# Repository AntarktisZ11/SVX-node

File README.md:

# SA6MBO SVX-node
A basic UHF or VHF node designed around a SA868 fitted as a HAT on top of an [Orange Pi Zero LTS](http://www.orangepi.org/html/hardWare/computerAndMicrocontrollers/details/Orange-Pi-Zero-LTS.html "Orange Pi Zero LTS"). The repeater software is the [SVXLink project](https://github.com/sm0svx/svxlink "SVXLink project") with configuration inspired by the [ROLink community](http://www.439100.ro/ "ROLink community"). The origin of this project is courtesy of [SM6TZL](https://svxportal.sm2ampr.net/station_info.php?callsign=SM6TZL&no_header=true "SM6TZL")'s small mobile unit. A massive praise goes to VoltLogs [VoltNode](https://github.com/voltlog/VoltNode "VoltNode") for comprising the work into a manageable PCB along with short but good documentation.

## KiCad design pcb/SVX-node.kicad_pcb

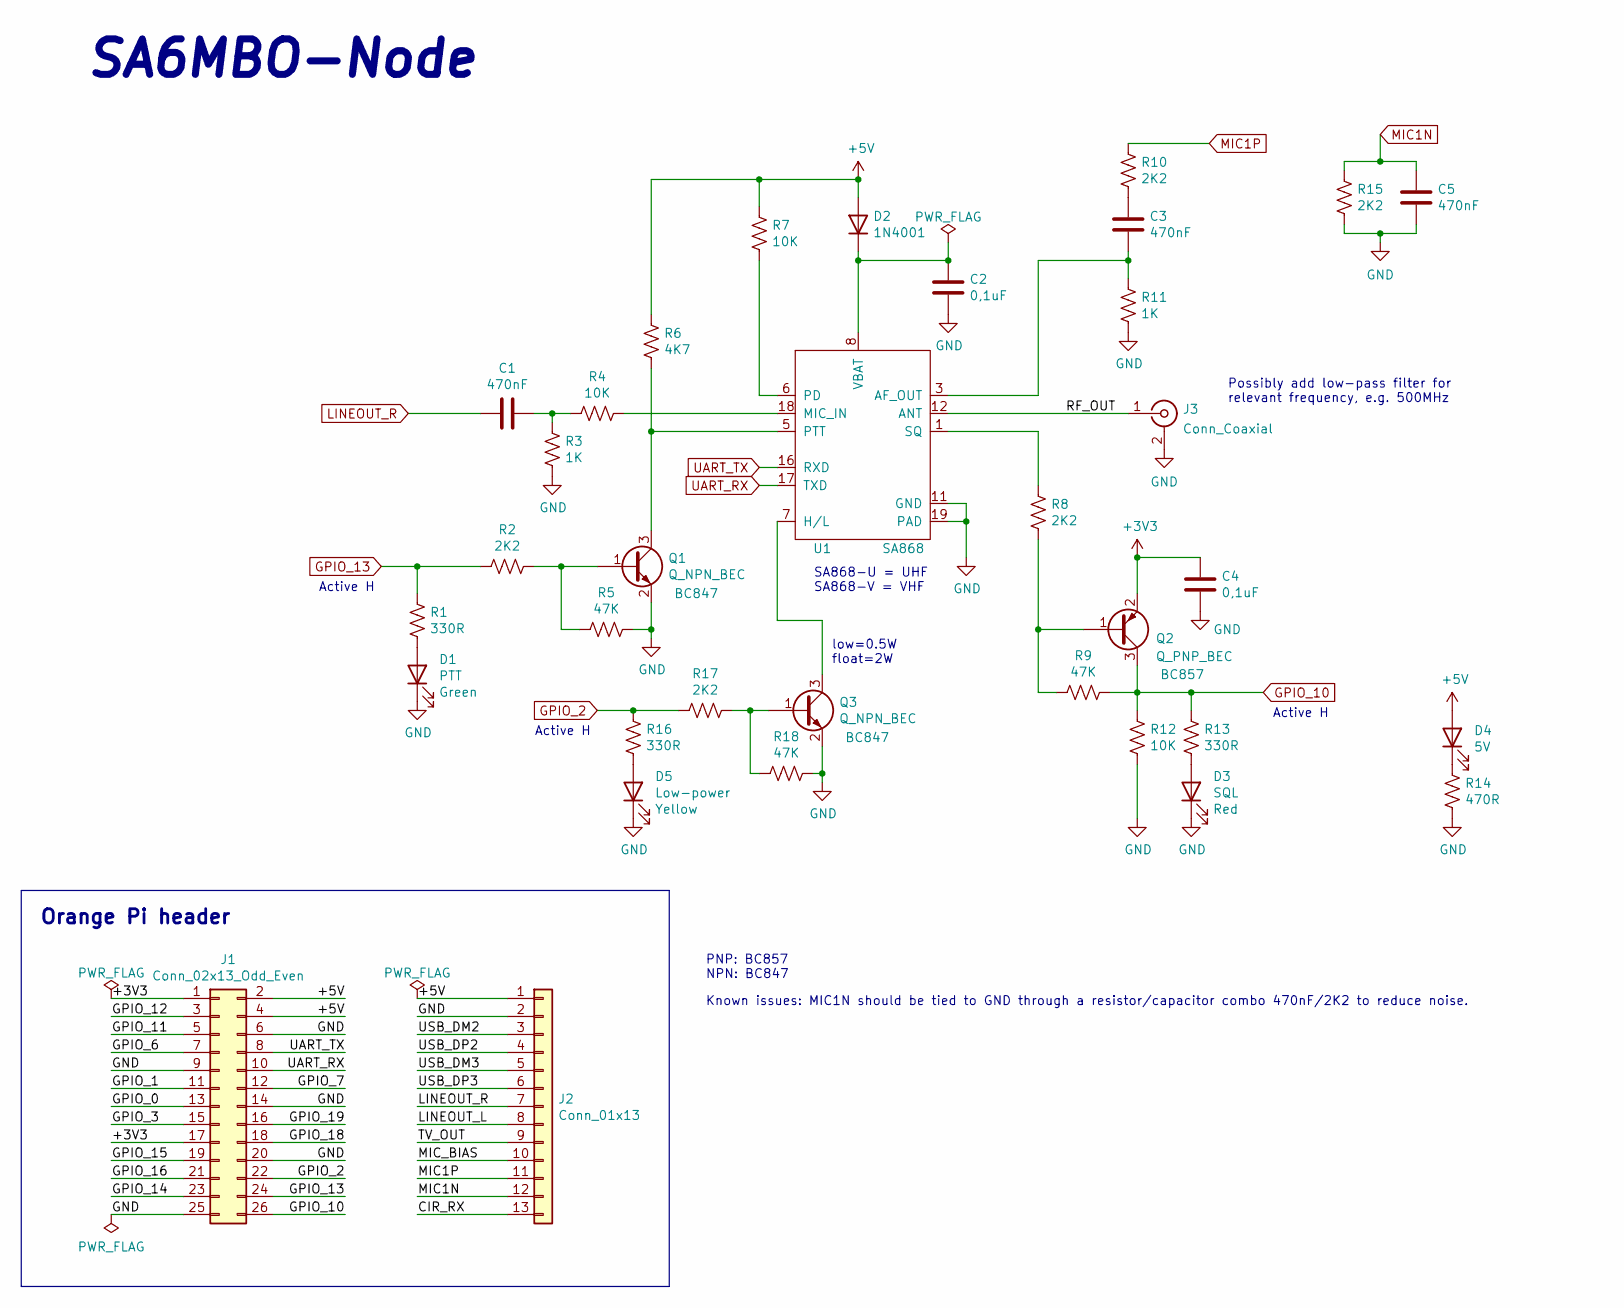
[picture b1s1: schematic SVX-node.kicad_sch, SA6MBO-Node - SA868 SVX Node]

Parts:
C1, C3, C5: 470nF; C_0603_1608Metric
C2, C4: 0,1uF; C_0603_1608Metric
D1: PTT; LED_0603_1608Metric
D2: 1N4001; D_DO-41_SOD81_P5.08mm_Vertical_KathodeUp
D3: SQL; LED_0603_1608Metric
D4: 5V; LED_0603_1608Metric
D5: Low-power; LED_0603_1608Metric
J1: Conn_02x13_Odd_Even; PinSocket_2x13_P2.54mm_Vertical
J2: Conn_01x13; PinSocket_1x13_P2.54mm_Vertical
J3: Conn_Coaxial; SMA_Amphenol_132291-12_Vertical
Q1, Q3: Q_NPN_BEC; TO-92_Inline_Wide
Q2: Q_PNP_BEC; TO-92_Inline_Wide
R1, R13, R16: 330R; R_0603_1608Metric
R2, R8, R10, R15, R17: 2K2; R_0603_1608Metric
R3, R11: 1K; R_0603_1608Metric
R4, R7, R12: 10K; R_0603_1608Metric
R5, R18: 47K; R_0603_1608Metric
R6: 4K7; R_0603_1608Metric
R9: 47K; R_Axial_DIN0204_L3.6mm_D1.6mm_P5.08mm_Horizontal
R14: 470R; R_0603_1608Metric
U1: SA868

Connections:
+3V3: C4.1, J1.1, J1.17, Q2.2 (E)
+5V: D2.2 (A), D4.2 (A), J1.2, J1.4, J2.1, R6.1, R7.1
/CIR_RX: J2.13
/GPIO_0: J1.13
/GPIO_1: J1.11
/GPIO_3: J1.15
/GPIO_6: J1.7
/GPIO_7: J1.12
/GPIO_11: J1.5
/GPIO_12: J1.3
/GPIO_14: J1.23
/GPIO_15: J1.19
/GPIO_16: J1.21
/GPIO_18: J1.18
/GPIO_19: J1.16
/LINEOUT_L: J2.8
/MIC_BIAS: J2.10
/RF_OUT: J3.1 (In), U1.12 (ANT)
/TV_OUT: J2.9
/USB_DM2: J2.3
/USB_DM3: J2.5
/USB_DP2: J2.4
/USB_DP3: J2.6
GND: C2.2, C4.2, C5.2, D1.1 (K), D3.1 (K), D5.1 (K), J1.6, J1.9, J1.14, J1.20, J1.25, J2.2, J3.2 (Ext), Q1.2 (E), Q3.2 (E), R3.2, R5.1, R11.2, R12.2, R14.2, R15.2, R18.1, U1.9, U1.10, U1.11 (GND), U1.19 (PAD)
GPIO_2: J1.22, R16.1, R17.2
GPIO_10: J1.26, Q2.3 (C), R9.2, R12.1, R13.1
GPIO_13: J1.24, R1.1, R2.2
LINEOUT_R: C1.2, J2.7
MIC1N: C5.1, J2.12, R15.1
MIC1P: J2.11, R10.1
unnamed: C1.1, R3.1, R4.2
unnamed: C2.1, D2.1 (K), U1.8 (VBAT)
unnamed: C3.1, R10.2
unnamed: C3.2, R11.1, U1.3 (AF_OUT)
unnamed: D1.2 (A), R1.2
unnamed: D3.2 (A), R13.2
unnamed: D4.1 (K), R14.1
unnamed: D5.2 (A), R16.2
unnamed: Q1.1 (B), R2.1, R5.2
unnamed: Q1.3 (C), R6.2, U1.5 (PTT)
unnamed: Q2.1 (B), R8.2, R9.1
unnamed: Q3.1 (B), R17.1, R18.2
unnamed: Q3.3 (C), U1.7 (H/L)
unnamed: R4.1, U1.18 (MIC_IN)
unnamed: R7.2, U1.6 (PD)
unnamed: R8.1, U1.1 (SQ)
UART_RX: J1.10, U1.17 (TXD)
UART_TX: J1.8, U1.16 (RXD)

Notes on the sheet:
PNP: BC857 NPN: BC847
Orange Pi header
Active H
Possibly add low-pass filter for relevant frequency, e.g. 500MHz
Known issues: MIC1N should be tied to GND through a resistor/capacitor combo 470nF/2K2 to reduce noise.
SA868-U = UHF SA868-V = VHF
low=0.5W float=2W
SA6MBO-Node

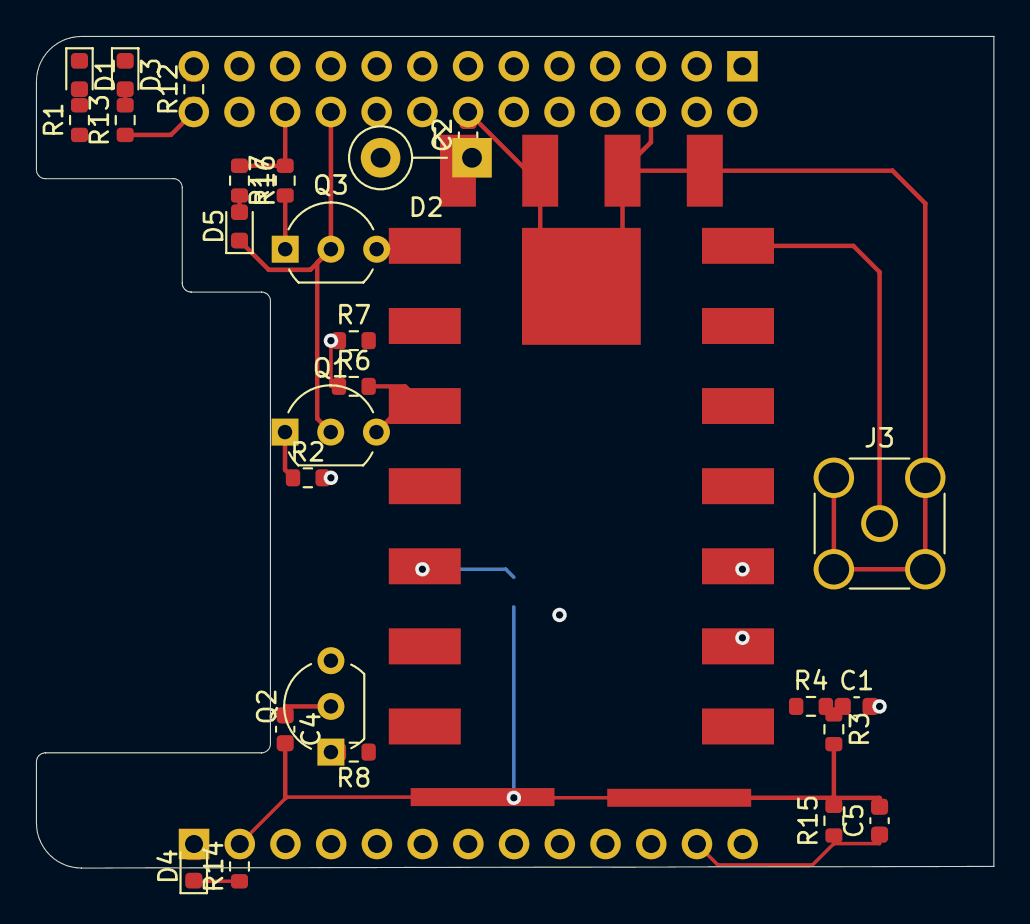
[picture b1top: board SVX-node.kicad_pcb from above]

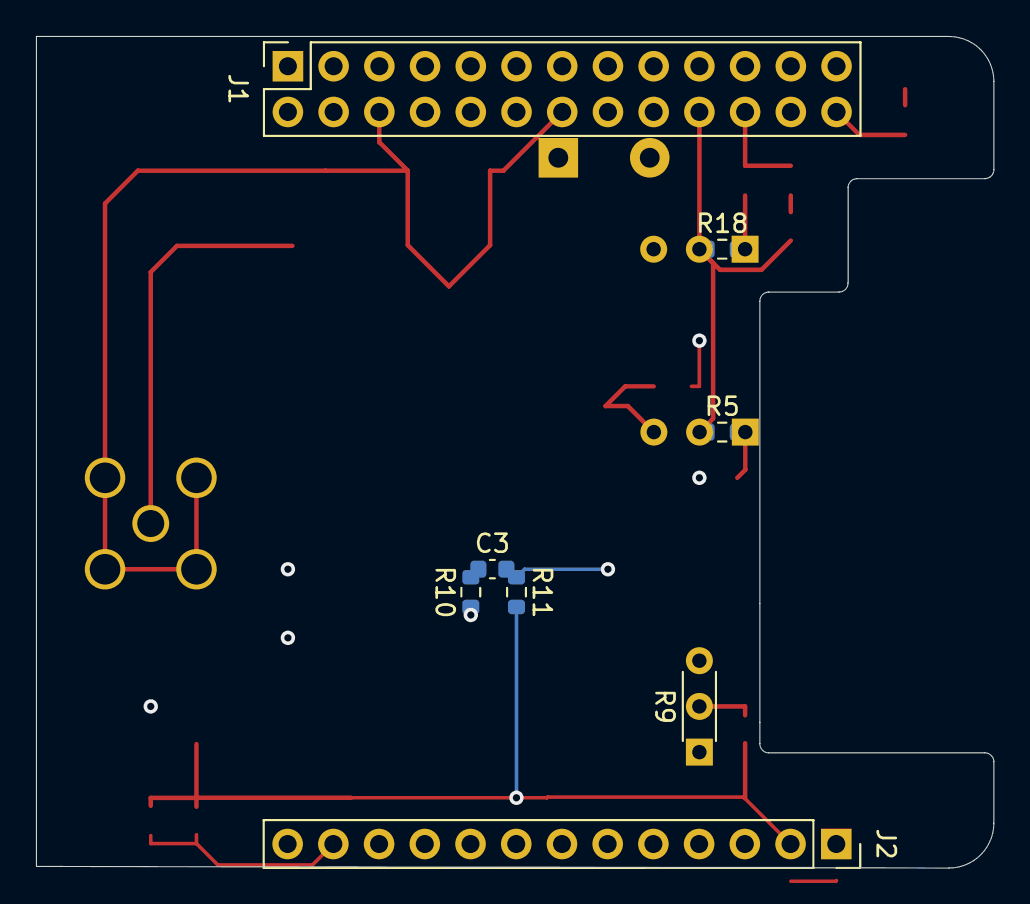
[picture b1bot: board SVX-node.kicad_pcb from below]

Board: 4 copper layers, 53.2 x 46.2 mm, 35 parts (8 on the bottom side), 28 nets.

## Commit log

2022-09-27 fix: replace broken SA818 component with new SA868
2022-09-30 feat: Finalize pcb layout for protoboard assembly
2022-10-02 fix: update submodule url to https
